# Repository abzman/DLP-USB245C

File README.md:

Updated version of the DLP-USB245R, with added USB C

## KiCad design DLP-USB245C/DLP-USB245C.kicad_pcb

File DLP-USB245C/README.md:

# DLP-USB245C

A USB-C, FT245RNL-based module that fits the 24-pin, 0.6" DIP footprint of the DLP-USB245M (FT245BM/BL). Revision 0.1 is a draft: schematic done, PCB outline and pins placed, nothing routed yet.

## Contents
| File | What it is |
|---|---|
| `DLP-USB245C.kicad_pro` | Project file (KiCad 8 or newer) |
| `DLP-USB245C.kicad_sch` | Schematic. Parts connect through net labels: labels with the same name are the same net. |
| `DLP-USB245C.kicad_pcb` | 2-layer board, 17.78 × 38.10 mm. The 24 module pins are already placed and linked to J1. |
| `DLP245C.kicad_sym`, `DLP245C.pretty/` | Project symbols, plus the module-pin footprint (1.0 mm drill) |
| `sym-lib-table`, `fp-lib-table` | Point KiCad at the project libraries |
| `BOM.csv` | Parts list with suggested manufacturer part numbers. DNP marks parts left unpopulated. |
| `netlist_check.txt` | Every net with its members, for review |

## Finishing the board
1. Open the `.kicad_pro` file and run ERC in the schematic.
2. In the PCB editor, run **Tools → Update PCB from Schematic (F8)**. This pulls the rest of the footprints from KiCad's standard libraries, and J1 stays where it is.
3. Place the parts. USB-C (J2) goes on the edge at the pin 12/13 end. The FT245RNL fits between the pin rows on the top side, and the passives can go on the bottom.
4. Route D+/D- as a 90 Ω differential pair, add a GND pour on both layers, then run DRC.

## Pin mapping (module pin → FT245RNL)
| Module pin | Signal | Connection |
|---|---|---|
| 1 | BOARD ID | GND (low means the 245 variant) |
| 2, 5, 7 | GND | GND |
| 3 | RESET# | U1 pin 19 |
| 4 | RESETO# | U3 MCP121 open-drain output, with R3 pull-up to 3V3 (see note 2) |
| 6 | 3V3OUT | U1 pin 17 (up to 50 mA) |
| 8 | SLEEP | U1 pin 12 PWREN#, with R5 10k pull-up to VCCIO |
| 9 | SND/WUP | **Not connected** (see note 1) |
| 10 | VCC-IO | U1 pin 4 (1.8 to 5.25 V) |
| 11 | EXTVCC | Through FB1 to U1 pin 20 VCC |
| 12 | PORTVCC | USB-C VBUS through F1 (500 mA PTC) |
| 13–16 | RXF#, TXE#, WR, RD# | U1 pins 23, 22, 14, 13 |
| 17–24 | D7…D0 | U1 pins 6, 10, 9, 2, 11, 3, 5, 1 |

## Differences from the original
1. **SND/WUP (pin 9):** the FT245R has no SI/WU pin, so the send-immediate function is not available. For remote wake, the FT245R uses RXF#: strobe it low for at least 20 ms while the bus is suspended.
2. **RESETO# (pin 4):** this is emulated by U3. It stays low until VCC rises above 4.38 V, then releases 120 ms later and is pulled up to 3.3 V. Unlike the FT245BM, the RESET# input does not drive it.
3. **Buffers:** the FIFO sizes differ from the FT245BM. Code that only uses the TXE#/RXF# handshake is unaffected.
4. **Jumpers:** JP1 (PORTVCC↔EXTVCC) and JP2 (EXTVCC↔VCC-IO) are open by default, so the board behaves exactly like the original. Close them to run a bus-powered 5 V setup without wiring straps on the host board.
5. **USB identity:** the default VID/PID is 0403:6001, the same as the FT245BM. If host software opens the device by description, set the description string with FT_PROG.

## Check before fabrication
- None of these files has been opened in KiCad yet. If anything fails to load, re-save from KiCad.
- Check that the stock footprint names in the BOM exist in your KiCad version. In particular, check that the GCT USB4105 footprint's pad names match the symbol pins A1…B12 and S1.
- The 17.78 × 38.10 mm (0.70" × 1.50") outline comes from DLP's *preliminary* drawing. Measure a real module with calipers, including which end the USB jack sits on.
- Read FTDI's "Migrating from FT2xxR to FT2xxRN" app note and the RN errata.

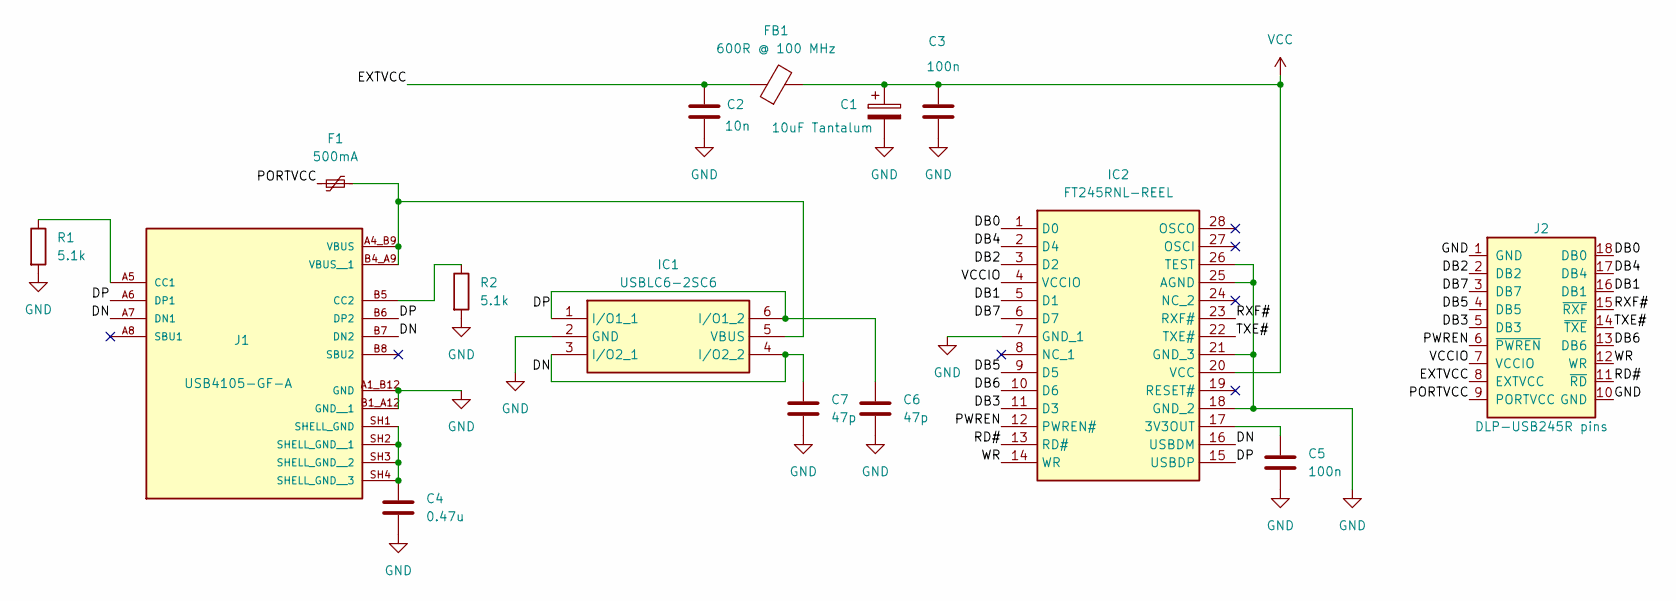
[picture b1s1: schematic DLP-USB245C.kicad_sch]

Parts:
C1: 10uF Tantalum; CAPPM3528X210N
C2: 10n; C_0603_1608Metric_Pad1.08x0.95mm_HandSolder
C3, C5: 100n; C_0603_1608Metric_Pad1.08x0.95mm_HandSolder
C4: 0.47u; C_0603_1608Metric_Pad1.08x0.95mm_HandSolder
C6, C7: 47p; C_0603_1608Metric_Pad1.08x0.95mm_HandSolder
F1: 500mA; FUSC2214X85N
FB1: 600R @ 100 MHz; R_0805_2012Metric_Pad1.20x1.40mm_HandSolder
IC1: USBLC6-2SC6; SOT95P280X145-6N; Mouser Part Number 511-USBLC6-2SC6
IC2: FT245RNL-REEL; SOP65P780X200-28N; Mouser Part Number 895-FT245RNL-REEL
J1: USB4105-GF-A; GCT_USB4105-GF-A; MPN USB4105-GF-A
J2: DLP-USB245R pins; Module18_W7.62mm_SMD_Bottom
R1, R2: 5.1k; R_0603_1608Metric_Pad0.98x0.95mm_HandSolder

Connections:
/DB0: IC2.1 (D0), J2.18 (DB0)
/DB1: IC2.5 (D1), J2.16 (DB1)
/DB2: IC2.3 (D2), J2.2 (DB2)
/DB3: IC2.11 (D3), J2.5 (DB3)
/DB4: IC2.2 (D4), J2.17 (DB4)
/DB5: IC2.9 (D5), J2.4 (DB5)
/DB6: IC2.10 (D6), J2.13 (DB6)
/DB7: IC2.6 (D7), J2.3 (DB7)
/DN: C7.1, IC1.3 (I/O2_1), IC1.4 (I/O2_2), IC2.16 (USBDM), J1.A7 (DN1), J1.B7 (DN2)
/DP: C6.1, IC1.1 (I/O1_1), IC1.6 (I/O1_2), IC2.15 (USBDP), J1.A6 (DP1), J1.B6 (DP2)
/EXTVCC: C2.1, FB1.1, J2.8 (EXTVCC)
/PORTVCC: F1.1, J2.9 (PORTVCC)
/PWREN: IC2.12 (PWREN#), J2.6 (~PWREN)
/RD#: IC2.13 (RD#), J2.11 (~RD)
/RXF#: IC2.23 (RXF#), J2.15 (~RXF)
/TXE#: IC2.22 (TXE#), J2.14 (~TXE)
/VCCIO: IC2.4 (VCCIO), J2.7 (VCCIO)
/WR: IC2.14 (WR), J2.12 (WR)
GND: C1.2, C2.2, C3.2, C4.2, C5.2, C6.2, C7.2, IC1.2 (GND), IC2.7 (GND_1), IC2.18 (GND_2), IC2.21 (GND_3), IC2.25 (AGND), IC2.26 (TEST), J1.A1_B12 (GND), J1.B1_A12 (GND__1), J2.1 (GND), J2.10 (GND), R1.2, R2.2
unnamed: F1.2, IC1.5 (VBUS), J1.A4_B9 (VBUS), J1.B4_A9 (VBUS__1)
unnamed: C5.1, IC2.17 (3V3OUT)
unnamed: J1.A5 (CC1), R1.1
unnamed: J1.B5 (CC2), R2.1
unnamed: C4.1, J1.SH1 (SHELL_GND), J1.SH2 (SHELL_GND__1), J1.SH3 (SHELL_GND__2), J1.SH4 (SHELL_GND__3)
VCC: C1.1, C3.1, FB1.2, IC2.20 (VCC)

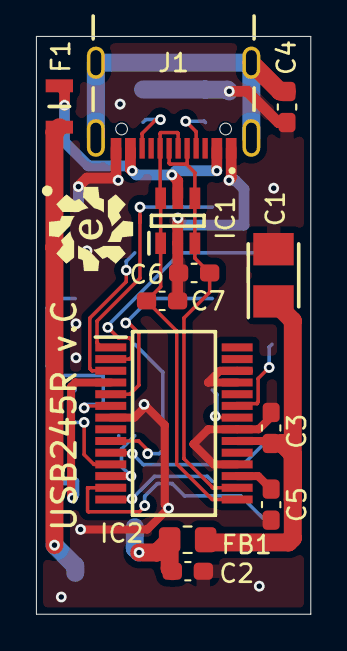
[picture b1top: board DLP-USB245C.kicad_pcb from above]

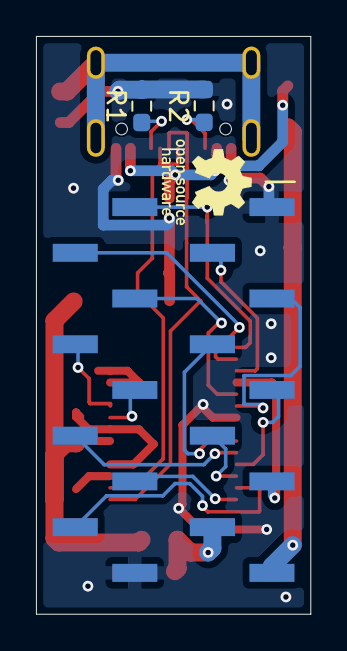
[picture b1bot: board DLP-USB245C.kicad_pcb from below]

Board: 2 copper layers, 15.2 x 32.1 mm, 15 parts (2 on the bottom side), 25 nets.
